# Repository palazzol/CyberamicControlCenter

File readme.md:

# Unofficial Cyberamic Control Center Archive #

This archive contains unofficial information about the Animatronics Control Computer designed the original Chuck E Cheese's Pizza Time Theatre.  The focus of this archive is to document the historical development and capabilities of this machine.

It was reused in several incarnations over it's lifetime:

## Reel to Reel Configuration: ##
* Based on a 6502 processor and a TEAC Tape Deck, this computer controller the shows such as Dolli Dimples, The Beagles, The King, and the Balcony Stage.

## SVHS Configuration #1: ##
* This same hardware was adapted to play media from SVHS Media.

## SVHS Configuration #2: ##
* Upgraded with a M68HC11 processor, and an external media switcher, this continued to be used to play SVHS media.

## DVD Configuration: ##
* Adapted to DVD Media

If you have any more information or experience with this machine, and would like to help document it's history and behavior, please reach out!

# Latest protocol definitions as decoded from ROM images #
https://docs.google.com/spreadsheets/d/1zTHxSJqbsTTEe6A_9ltzb_rc91lcfIUvdmzVYEThIzg/edit?usp=sharing

# Questions: #

We're working on collecting as much information on how the original Pizza Time Theater system worked and have generated some questions:

* Did the original R2R system use 4-track audio at any stores?

Backplane:
* Was the original card cage a different size to accomodate the 0004 rev.a card?
* Why is the lights 50-pin connector recessed on the card compared to the character card?

Are there more board revisions beyond what we have? looking for:
* Audio board 0003 rev.a, rev.b, and beyond rev.c
* Audio board 0033 rev.b and beyond
* Character board 0004 rev.c and beyond
* Character board 0034 rev.b, rev.f and beyond
* Light board 0021 rev.b to rev.e
* Transport board 0020 rev.a
* Did the original transport card take a external uart clock? per the schematic
* Transport board 0020 rev.c
* CPU board 0001 rev.d and beyond 
* Random movements board?
* Board 0002?

Where are any other rom variants beyond what's in this archive?
* (We strongly believe the original balcony stage rom is not represented here)
* How do the other ROMs handle the buttons on the front panel?

Any more un-scanned documentation?
* Are there any more schematics? 
* Any documentation on how to hook up all the shows?

More show tapes on original media?
* More shows decoded?
* What are the formats for the decoding?
* Is there any metadata they missed like potentially more tracks?

Who else to talk to on this subject?

Extra parts we don't have?

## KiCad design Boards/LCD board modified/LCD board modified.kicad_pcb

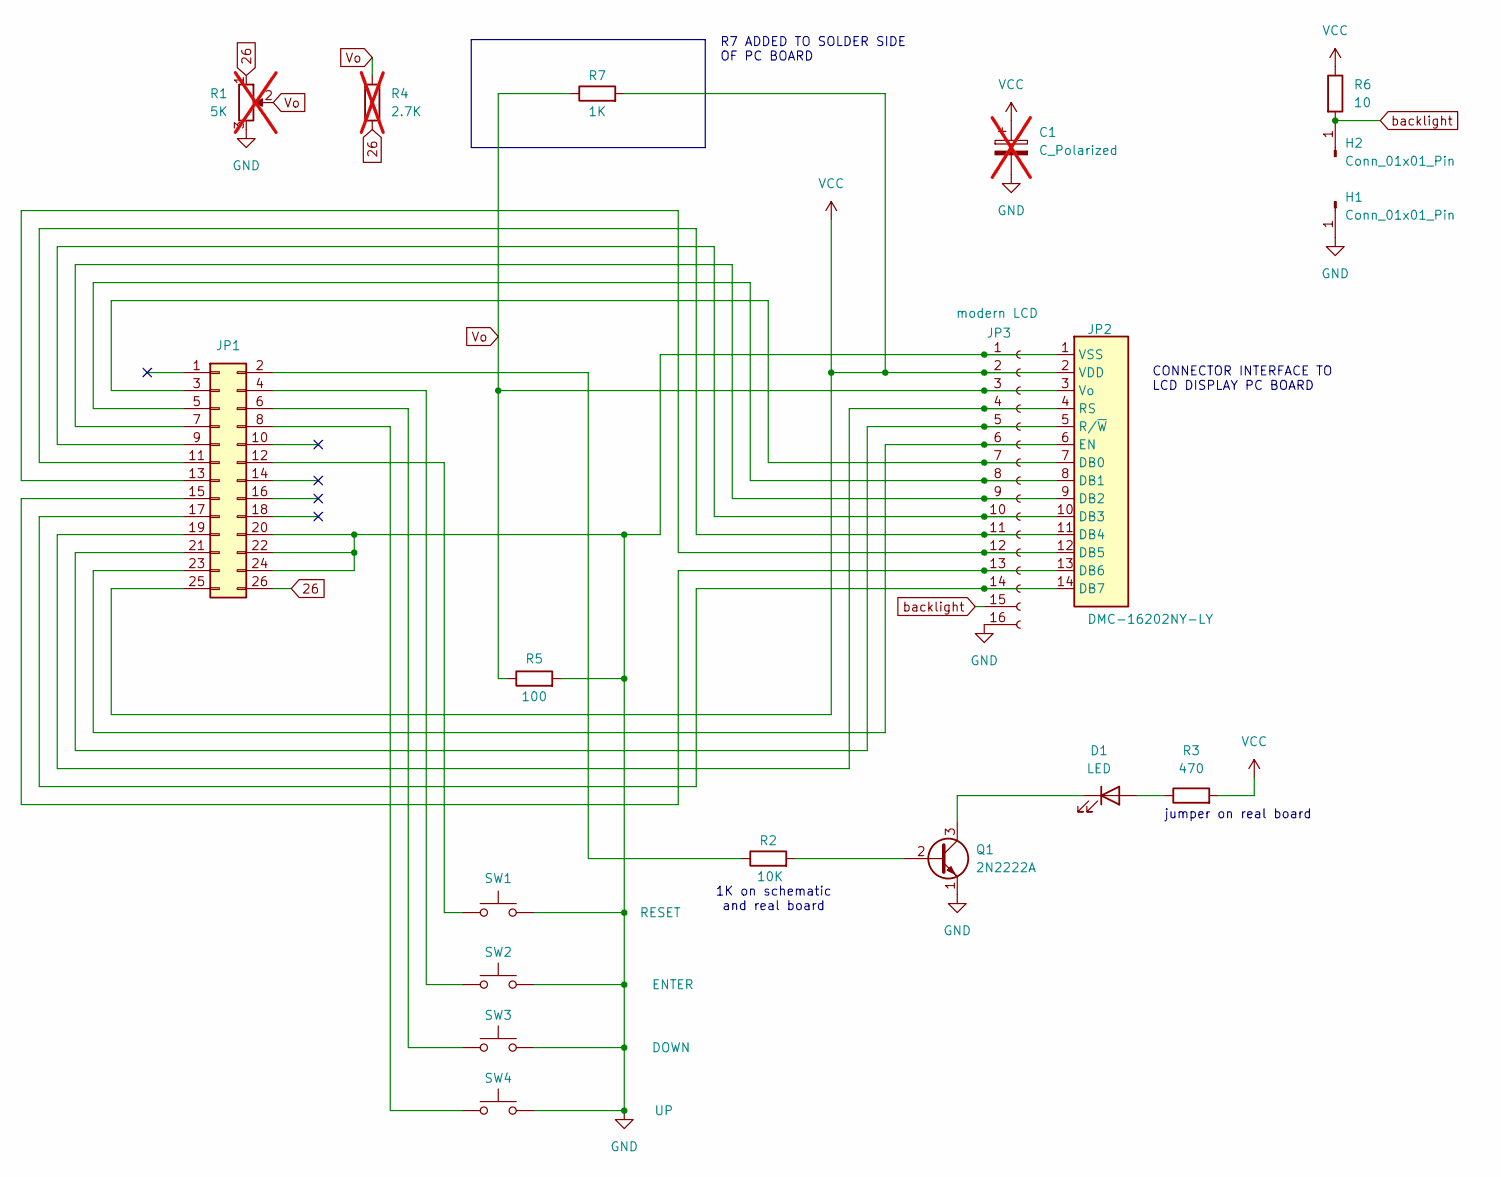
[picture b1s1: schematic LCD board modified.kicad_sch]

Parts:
C1: C_Polarized; CP_Radial_D8.0mm_P5.00mm; not fitted
D1: LED; PinHeader_1x02_P2.54mm_Vertical
H1, H2: Conn_01x01_Pin
JP1: Conn_02x13_Odd_Even; PinHeader_2x13_P2.54mm_Vertical
JP2: DMC-16202NY-LY; CEC LCD
JP3: modern LCD; PinHeader_1x16_P2.54mm_Vertical
Q1: 2N2222A; TO-18-3
R1: 5K; Potentiometer_Bourns_3006P_Horizontal; not fitted
R2: 10K; R_Axial_DIN0207_L6.3mm_D2.5mm_P10.16mm_Horizontal
R3: 470; R_Axial_DIN0207_L6.3mm_D2.5mm_P10.16mm_Horizontal
R4: 2.7K; R_Axial_DIN0207_L6.3mm_D2.5mm_P10.16mm_Horizontal; not fitted
R5: 100; R_Axial_DIN0207_L6.3mm_D2.5mm_P10.16mm_Horizontal
R6: 10; R_Axial_DIN0207_L6.3mm_D2.5mm_P10.16mm_Horizontal
R7: 1K; R_Axial_DIN0207_L6.3mm_D2.5mm_P10.16mm_Horizontal
SW1: RESET; CEC LCD pushbutton
SW2: ENTER; CEC LCD pushbutton
SW3: DOWN; CEC LCD pushbutton
SW4: UP; CEC LCD pushbutton

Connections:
26: JP1.26, R1.1, R4.2
GND: C1.2, H1.1, JP1.20, JP1.22, JP1.24, JP2.1 (VSS), JP3.1, JP3.16, Q1.1 (E), R1.3, R5.2, SW1.1, SW2.2, SW3.2, SW4.2
unnamed: D1.2 (A), R3.1
unnamed: D1.1 (K), Q1.3 (C)
unnamed: JP1.2, R2.1
unnamed: JP1.3, JP2.7 (DB0), JP3.7
unnamed: JP1.4, SW2.1
unnamed: JP1.5, JP2.8 (DB1), JP3.8
unnamed: JP1.6, SW3.1
unnamed: JP1.7, JP2.9 (DB2), JP3.9
unnamed: JP1.8, SW4.1
unnamed: JP1.9, JP2.10 (DB3), JP3.10
unnamed: JP1.11, JP2.11 (DB4), JP3.11
unnamed: JP1.12, SW1.2
unnamed: JP1.13, JP2.12 (DB5), JP3.12
unnamed: JP1.15, JP2.13 (DB6), JP3.13
unnamed: JP1.17, JP2.14 (DB7), JP3.14
unnamed: JP1.19, JP2.4 (RS), JP3.4
unnamed: JP1.21, JP2.5 (R/~W), JP3.5
unnamed: JP1.23, JP2.6 (EN), JP3.6
unnamed: Q1.2 (B), R2.2
VCC: C1.1, JP1.25, JP2.2 (VDD), JP3.2, R3.2, R6.1, R7.2
Vo: JP2.3 (Vo), JP3.3, R1.2, R4.1, R5.1, R7.1
backlight: H2.1, JP3.15, R6.2

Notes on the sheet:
1K on schematic and real board
R7 ADDED TO SOLDER SIDE OF PC BOARD
jumper on real board
CONNECTOR INTERFACE TO LCD DISPLAY PC BOARD

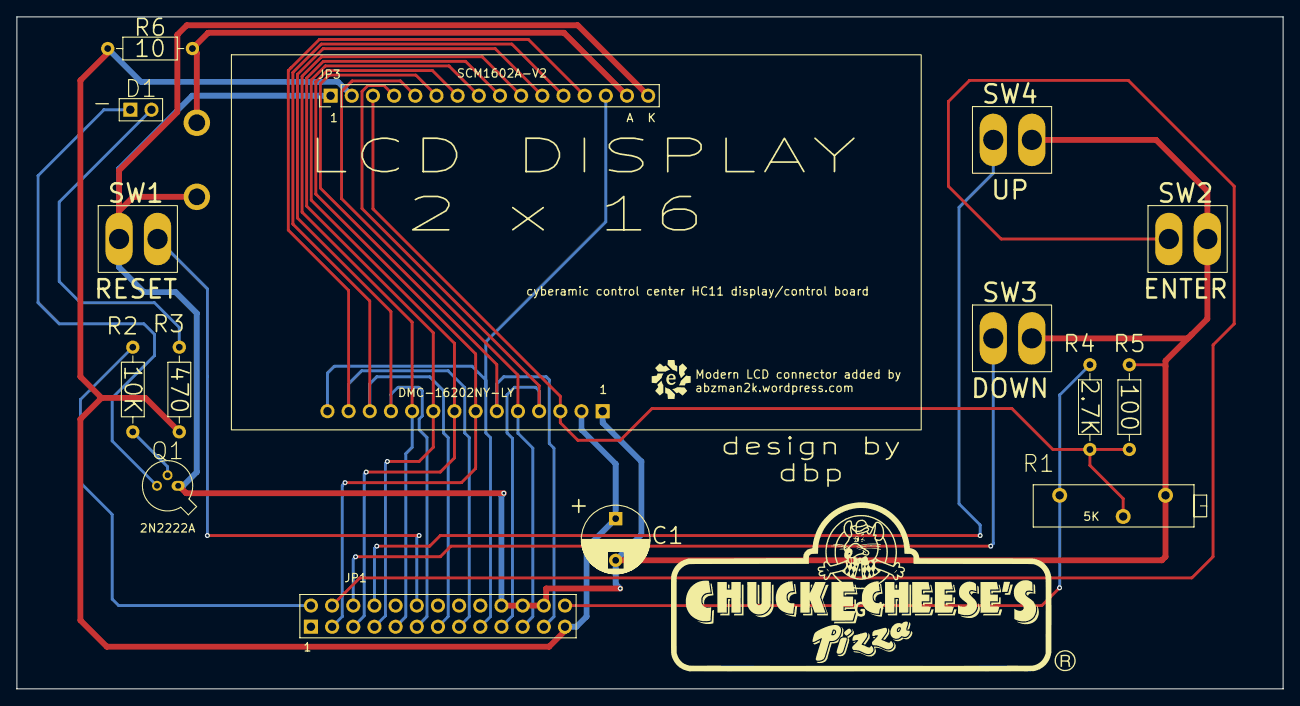
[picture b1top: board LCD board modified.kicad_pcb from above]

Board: 2 copper layers, 151.9 x 80.6 mm, 18 parts (0 on the bottom side), 24 nets.

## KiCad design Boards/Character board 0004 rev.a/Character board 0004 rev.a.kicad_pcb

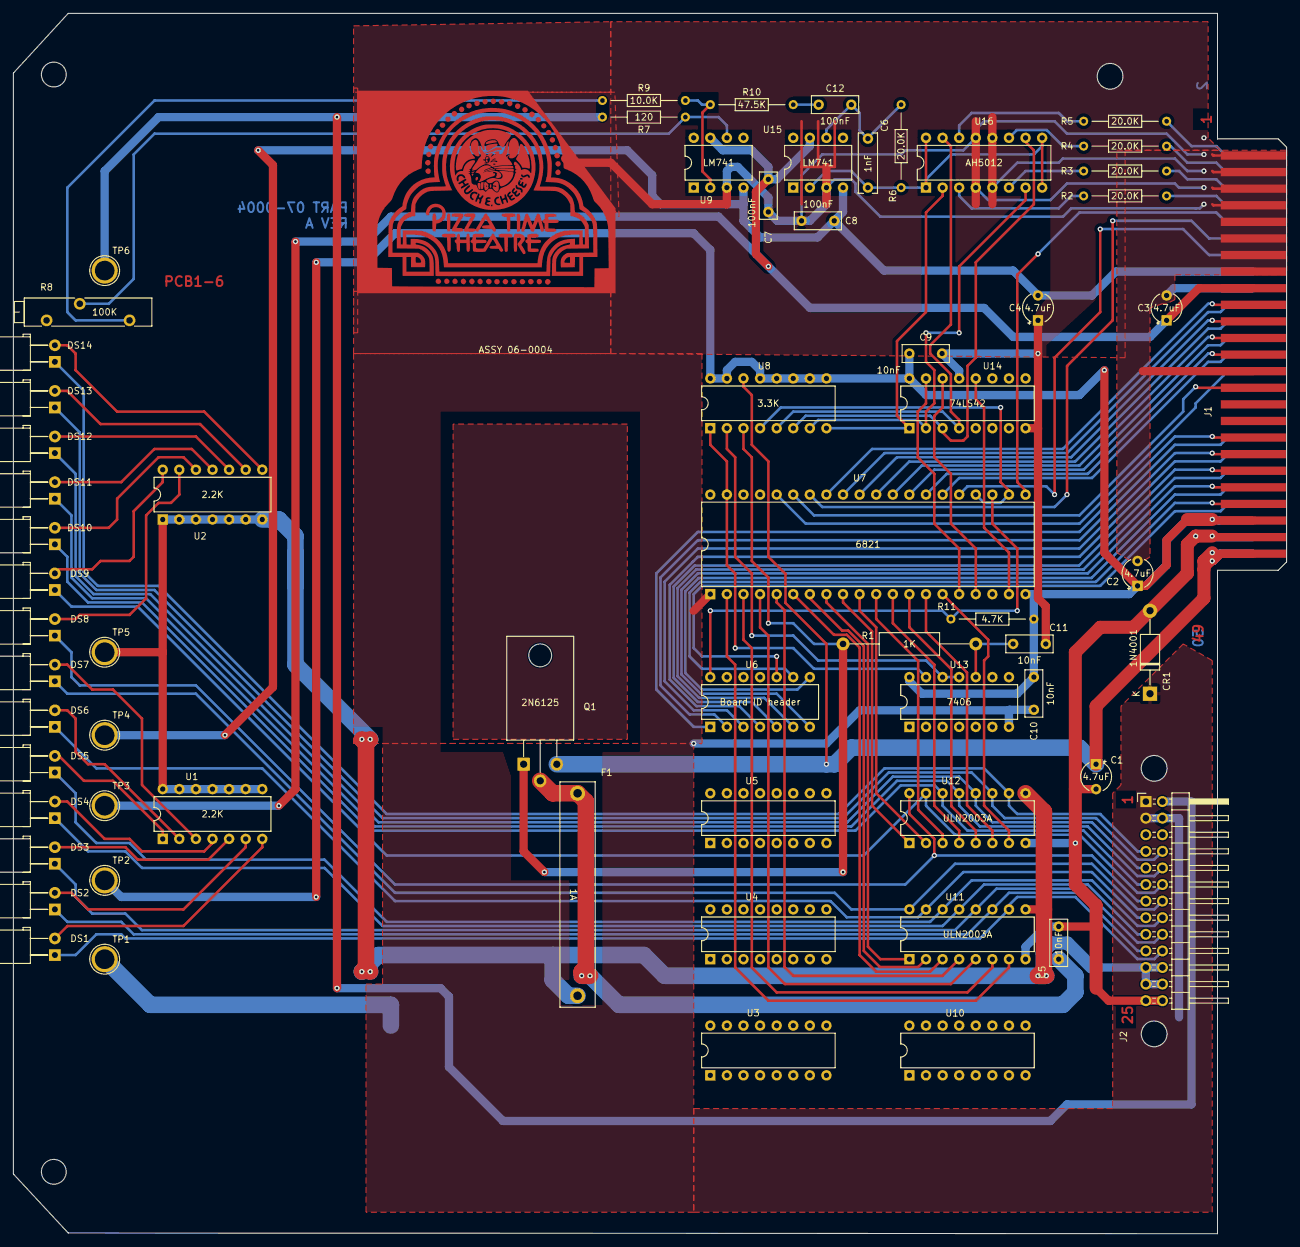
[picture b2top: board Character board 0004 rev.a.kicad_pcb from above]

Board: 2 copper layers, 194.9 x 186.8 mm, 65 parts (0 on the bottom side), 101 nets.

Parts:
C1, C2, C3, C4: 4.7uF; CP_Radial_Tantal_D4mm_P3.81mm
C5, C9, C10, C11: 10nF; C_Rect_L7.0mm_W2.5mm_P5.00mm
C6: 1nF; C_Rect_L9.0mm_W2.7mm_P7.50mm_MKT
C7, C8, C12: 100nF; C_Rect_L7.0mm_W2.5mm_P5.00mm
CR1: 1N4001; D_DO-41_SOD81_P12.70mm_Horizontal
DS1, DS2, DS3, DS4, DS5, DS6, DS7, DS8, DS9, DS10, DS11, DS12, DS13, DS14: LED; LED_D5.0mm_Horizontal_O3.81mm_Z15.0mm reversed
F1: 1A; Fuseholder_Littelfuse_445_030_series_5x30mm
G1: GND; PTT white
J1: card edge; Chuck_E_Cheese_small_card_edge
J2: character connector; PinHeader_2x13_P2.54mm_Horizontal
Q1: 2N6125; TO-220-3_Horizontal_TabDown
R1: 1K; R_Axial_DIN0309_L9.0mm_D3.2mm_P20.32mm_Horizontal
R2, R3, R4, R5, R6: 20.0K; R_Axial_DIN0204_L3.6mm_D1.6mm_P12.7mm_Horizontal
R7: 120; R_Axial_DIN0204_L3.6mm_D1.6mm_P12.7mm_Horizontal
R8: 100K; Potentiometer_Bourns_3005_Horizontal
R9: 10.0K; R_Axial_DIN0204_L3.6mm_D1.6mm_P12.7mm_Horizontal
R10: 47.5K; R_Axial_DIN0204_L3.6mm_D1.6mm_P12.7mm_Horizontal
R11: 4.7K; R_Axial_DIN0204_L3.6mm_D1.6mm_P12.7mm_Horizontal
TP1: GND; TestPoint_Plated_Hole_D3.0mm
TP2: +5; TestPoint_Plated_Hole_D3.0mm
TP3: +12; TestPoint_Plated_Hole_D3.0mm
TP4: -12; TestPoint_Plated_Hole_D3.0mm
TP5: 24; TestPoint_Plated_Hole_D3.0mm
TP6: AUD; TestPoint_Plated_Hole_D3.0mm
U1, U2: 2.2K; DIP-14_W7.62mm
U3, U4, U5, U10: Unused DIP; DIP-16_W7.62mm
U6: Board ID header; DIP-14_W7.62mm
U7: 6821; DIP-40_W15.24mm
U8: 3.3K; DIP-16_W7.62mm
U9, U15: LM741; DIP-8_W7.62mm
U11, U12: ULN2003A; DIP-16_W7.62mm
U13: 7406; DIP-14_W7.62mm
U14: 74LS42; DIP-16_W7.62mm
U16: AH5012; DIP-16_W7.62mm

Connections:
5V: C2.1, C9.1, C10.1, J1.45, J1.46, R11.1, TP2.1, U7.20 (VCC), U8.9 (R8.2), U8.10 (R7.2), U8.11 (R6.2), U8.12 (R5.2), U8.13 (R4.2), U8.15 (R2.2), U8.16 (R1.2), U13.14 (VCC), U14.16 (VCC)
5Vpu: U8.2 (R2.1), U13.11, U13.12
12V: C3.1, C7.1, J1.17, TP3.1, U9.7 (V+), U15.7 (V+)
24R: C1.2, C5.1, CR1.2 (A), J1.47, J1.48, J2.25, J2.26, U11.8 (GND), U12.8 (GND)
24V: C1.1, J1.49, J1.50, Q1.3 (E), U8.14 (R3.2)
24Vout: F1.2, J2.21, J2.22, J2.23, J2.24, TP5.1, U1.8 (R7.2), U1.9 (R6.2), U1.10 (R5.2), U1.11 (R4.2), U1.12 (R3.2), U1.13 (R2.2), U1.14 (R1.2), U2.1 (R1.1), U2.2 (R2.1), U2.3 (R3.1), U2.4 (R4.1), U2.5 (R5.1), U2.6 (R6.1), U2.7 (R7.1), U11.9 (COM), U12.9 (COM)
24Vpu: Q1.1 (B), R1.1, U8.3 (R3.1)
-12V: C4.2, C8.2, J1.16, TP4.1, U9.4 (V-), U15.4 (V-)
A0out: DS1.1 (K), J2.20, U11.10 (O7)
A1out: DS2.1 (K), J2.19, U11.11 (O6)
A2out: DS3.1 (K), J2.18, U11.12 (O5)
A3out: DS4.1 (K), J2.17, U11.13 (O4)
A4out: DS5.1 (K), J2.16, U11.14 (O3)
A5out: DS6.1 (K), J2.15, U11.15 (O2)
A6out: DS7.1 (K), J2.14, U11.16 (O1)
A7out: DS8.1 (K), J2.13, U12.16 (O1)
AUD: J2.2, R7.1, TP6.1
B0out: DS9.1 (K), J2.12, U12.15 (O2)
B1out: DS10.1 (K), J2.11, U12.14 (O3)
B2out: DS11.1 (K), J2.10, U12.13 (O4)
B3out: DS12.1 (K), J2.9, U12.12 (O5)
B4out: DS13.1 (K), J2.8, U12.11 (O6)
B5out: DS14.1 (K), J2.7, U12.10 (O7)
BA0: J1.28, U7.36 (RS0)
BA1: J1.29, U7.35 (RS1)
BGOUT_AGC: J1.8, R2.1
BS1: J1.35, U6.1
BS2: J1.36, U6.2
BS3: J1.37, U6.3
BS4: J1.38, U6.4
BS5: J1.39, U6.5
BS6: J1.40, U6.6
BS7: J1.41, U6.7
BS8: J1.42, U6.8
BS9: J1.43, U6.9
BS10: J1.44, U6.10
CA2: U7.39 (CA2), U8.1 (R1.1), U13.13
CB2: U7.19 (CB2), U14.12 (A3)
CS: U7.22 (CS0), U7.24 (CS1), U8.4 (R4.1)
DBB0: J1.19, U7.33 (D0)
DBB1: J1.20, U7.32 (D1)
DBB2: J1.21, U7.31 (D2)
DBB3: J1.22, U7.30 (D3)
DBB4: J1.23, U7.29 (D4)
DBB5: J1.24, U7.28 (D5)
DBB6: J1.25, U7.27 (D6)
DBB7: J1.26, U7.26 (D7)
GND: C2.2, C3.2, C4.1, C7.2, C8.1, C9.2, C10.2, C11.2, CR1.1 (K), G1.1, J1.1, J1.3, J1.5, J1.7, J1.9, J1.11, J1.13, J1.15, J1.18, J1.27, J2.1, J2.3, J2.4, TP1.1, U7.1 (VSS), U9.3 (+), U13.7 (GND), U14.8 (GND), U14.13 (A2), U15.3 (+), U16.4, U16.5, U16.12, U16.13
unnamed: C11.1, R1.2, U13.10
unnamed: C12.1, R10.2
unnamed: C6.2, C12.2, R6.2, U15.6
unnamed: DS1.2 (A), U1.7 (R7.1)
unnamed: DS2.2 (A), U1.6 (R6.1)
unnamed: DS3.2 (A), U1.5 (R5.1)
unnamed: DS4.2 (A), U1.4 (R4.1)
unnamed: DS5.2 (A), U1.1 (R1.1)
unnamed: DS6.2 (A), U1.2 (R2.1)
unnamed: DS7.2 (A), U1.3 (R3.1)
unnamed: DS8.2 (A), U2.13 (R2.2)
unnamed: DS9.2 (A), U2.14 (R1.2)
unnamed: DS10.2 (A), U2.12 (R3.2)
unnamed: DS11.2 (A), U2.11 (R4.2)
unnamed: DS12.2 (A), U2.10 (R5.2)
unnamed: DS13.2 (A), U2.9 (R6.2)
unnamed: DS14.2 (A), U2.8 (R7.2)
unnamed: C5.2, F1.1, Q1.2 (C)
unnamed: R2.2, U16.3
unnamed: R3.2, U16.6
unnamed: R4.2, U16.11
unnamed: R5.2, U16.14
unnamed: R7.2, R8.2, U9.6
unnamed: R8.1, R9.1
unnamed: R11.2, U6.14, U7.23 (~CS2)
unnamed: R9.2, R10.1, U9.2 (-)
unnamed: U8.8 (R8.1), U14.1 (0), U16.2
unnamed: U8.7 (R7.1), U14.2 (1), U16.7
unnamed: U8.6 (R6.1), U14.3 (2), U16.10
unnamed: U8.5 (R5.1), U14.4 (3), U16.15
unnamed: C6.1, R6.1, U15.2 (-), U16.1, U16.8, U16.9, U16.16
PA0: U7.2 (PA0), U11.7 (I7)
PA1: U7.3 (PA1), U11.6 (I6)
PA2: U7.4 (PA2), U11.5 (I5)
PA3: U7.5 (PA3), U11.4 (I4)
PA4: U7.6 (PA4), U11.3 (I3)
PA5: U7.7 (PA5), U11.2 (I2)
PA6: U7.8 (PA6), U11.1 (I1)
PA7: U7.9 (PA7), U12.1 (I1)
PB0: U7.10 (PB0), U12.2 (I2)
PB1: U7.11 (PB1), U12.3 (I3)
PB2: U7.12 (PB2), U12.4 (I4)
PB3: U7.13 (PB3), U12.5 (I5)
PB4: U7.14 (PB4), U12.6 (I6)
PB5: U7.15 (PB5), U12.7 (I7)
PB6: U7.16 (PB6), U14.15 (A0)
PB7: U7.17 (PB7), U14.14 (A1)
PHI2: J1.14, U7.25 (ENABLE)
R2R_audio_AGC: J1.6, R3.1
R/~W: J1.10, U7.21 (R/~W)
aux1_AGC: J1.2, R5.1
aux2_AGC: J1.4, R4.1
~MRST: J1.12, U7.34 (~RESET)

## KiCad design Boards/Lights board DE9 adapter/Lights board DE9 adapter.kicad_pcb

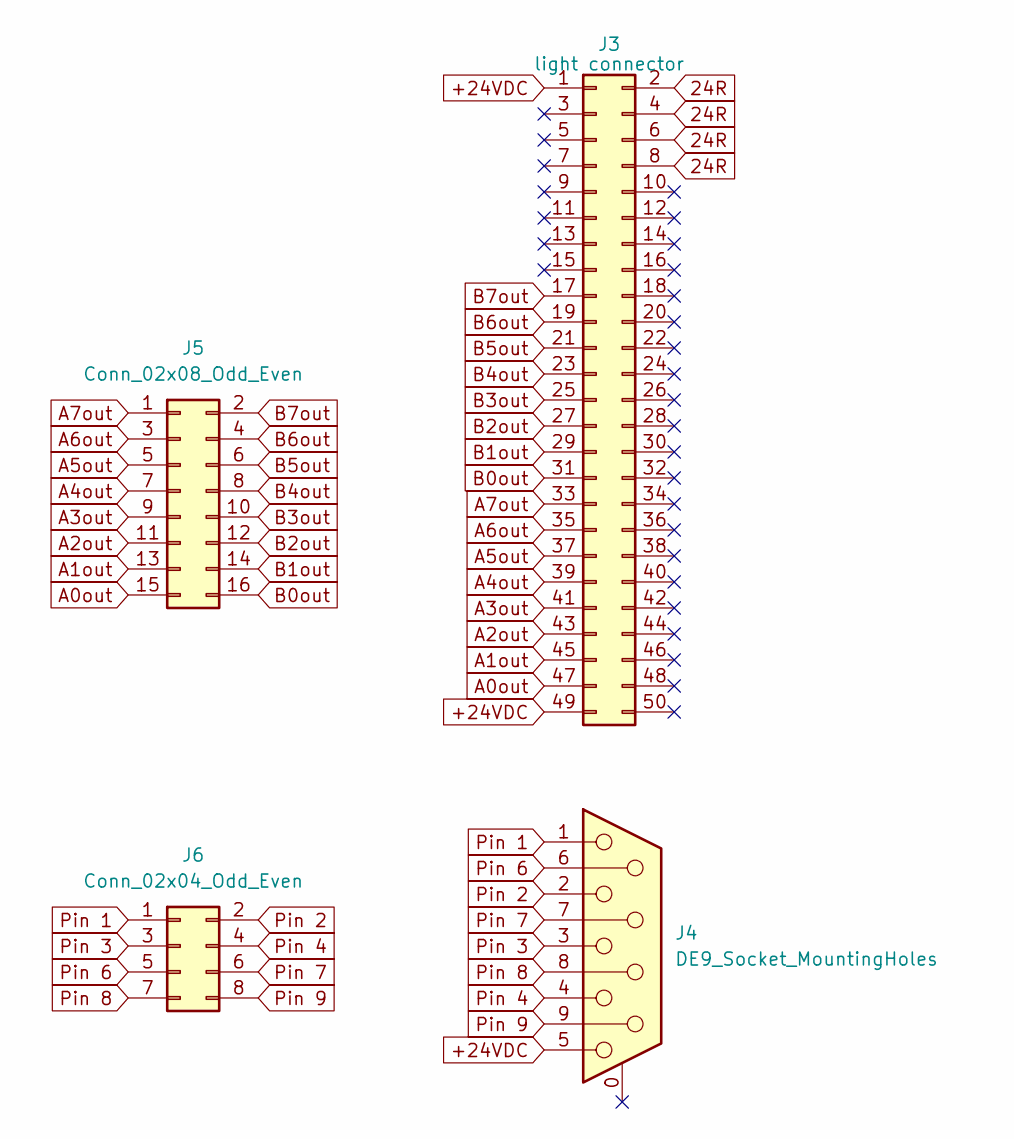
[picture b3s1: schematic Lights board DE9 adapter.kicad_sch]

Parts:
J3: light connector; PinSocket_2x25_P2.54mm_Horizontal
J4: DE9_Socket_MountingHoles; DSUB-9_Socket_Horizontal_P2.77x2.84mm_EdgePinOffset7.70mm_H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
J5: Conn_02x08_Odd_Even; PinHeader_2x08_P2.54mm_Horizontal
J6: Conn_02x04_Odd_Even; PinHeader_2x04_P2.54mm_Horizontal

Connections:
24R: J3.2, J3.4, J3.6, J3.8
+24VDC: J3.1, J3.49, J4.5
A0out: J3.47, J5.15
A1out: J3.45, J5.13
A2out: J3.43, J5.11
A3out: J3.41, J5.9
A4out: J3.39, J5.7
A5out: J3.37, J5.5
A6out: J3.35, J5.3
A7out: J3.33, J5.1
B0out: J3.31, J5.16
B1out: J3.29, J5.14
B2out: J3.27, J5.12
B3out: J3.25, J5.10
B4out: J3.23, J5.8
B5out: J3.21, J5.6
B6out: J3.19, J5.4
B7out: J3.17, J5.2
Pin 1: J4.1, J6.1
Pin 2: J4.2, J6.2
Pin 3: J4.3, J6.3
Pin 4: J4.4, J6.4
Pin 6: J4.6, J6.5
Pin 7: J4.7, J6.6
Pin 8: J4.8, J6.7
Pin 9: J4.9, J6.8

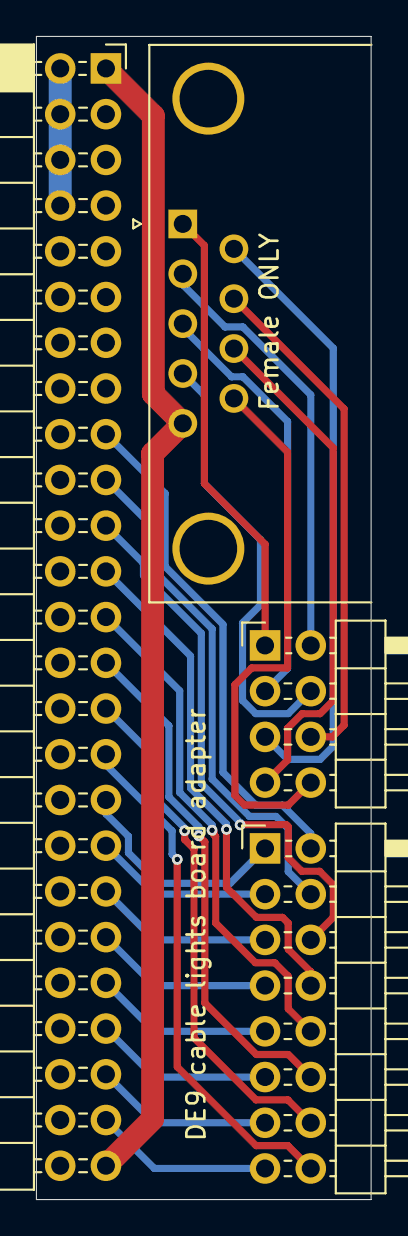
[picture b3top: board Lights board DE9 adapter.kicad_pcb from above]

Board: 2 copper layers, 18.6 x 64.6 mm, 4 parts (0 on the bottom side), 26 nets.

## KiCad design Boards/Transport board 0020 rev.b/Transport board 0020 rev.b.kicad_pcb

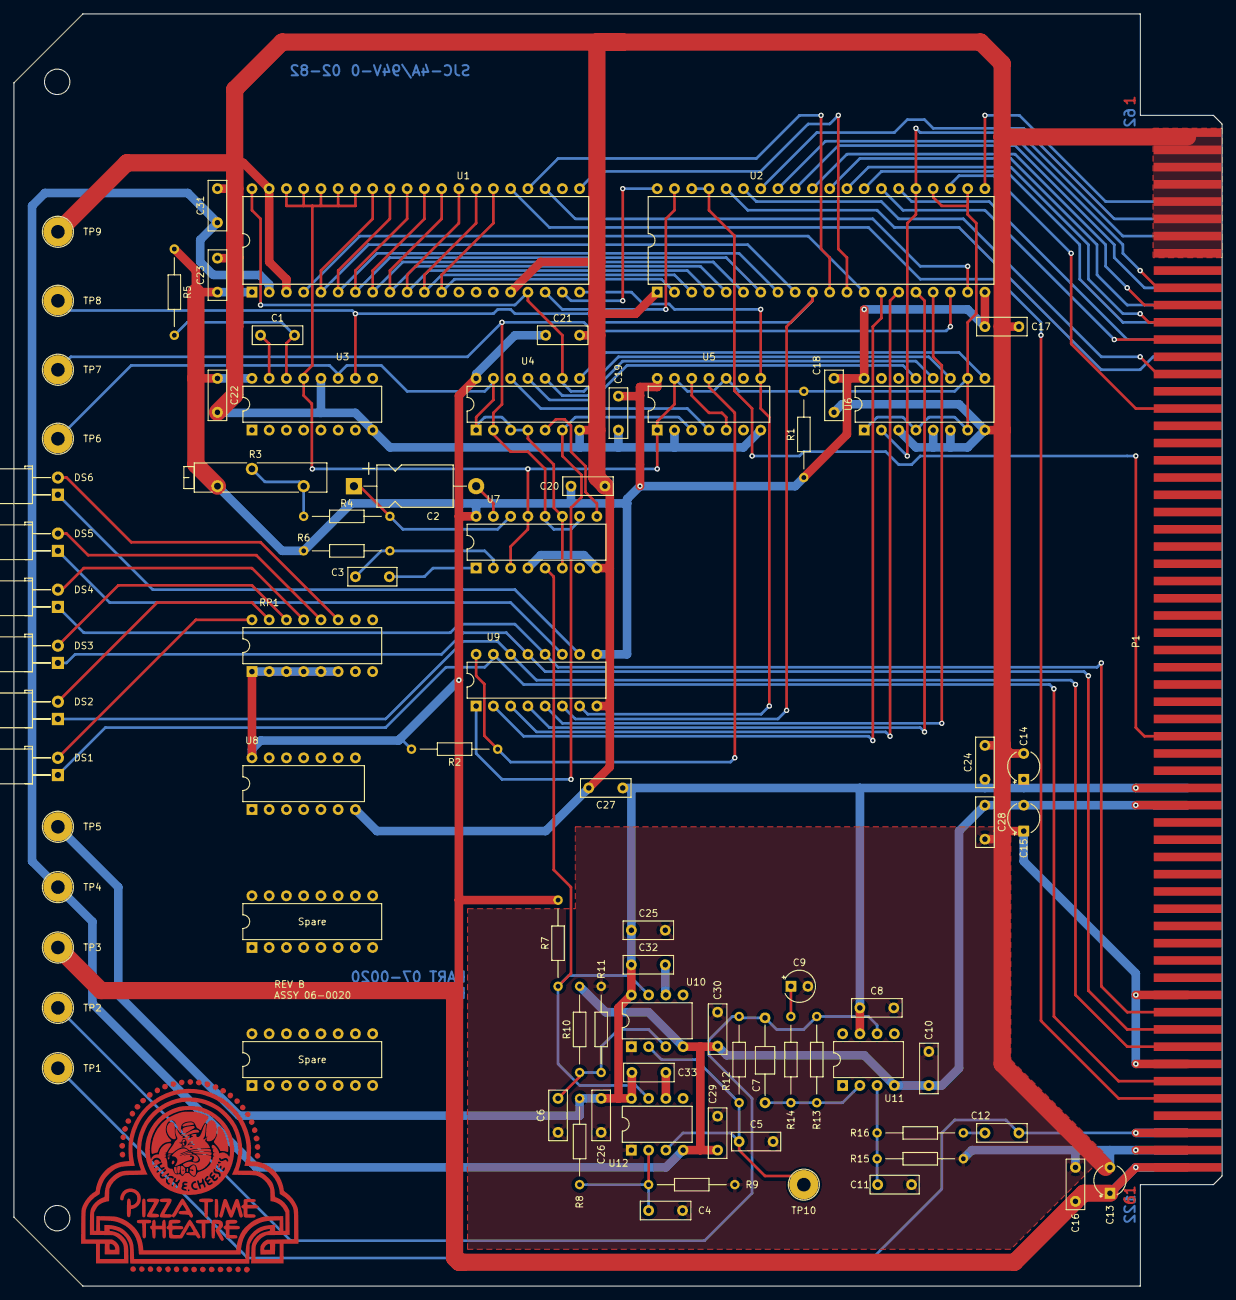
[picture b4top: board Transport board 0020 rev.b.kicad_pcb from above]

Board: 2 copper layers, 177.9 x 187.4 mm, 81 parts (0 on the bottom side), 83 nets.

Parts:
C1: 50nF; C_Rect_L7.2mm_W2.5mm_P5.00mm_FKS2_FKP2_MKS2_MKP2
C2: 39nF; CP_Axial_L11.0mm_D6.0mm_P18.00mm_Horizontal
C3, C5, C11: 100pF; C_Rect_L7.0mm_W2.5mm_P5.00mm
C4, C6, C8, C10, C12, C32, C33: 100nF; C_Rect_L7.2mm_W2.5mm_P5.00mm_FKS2_FKP2_MKS2_MKP2
C7: 3300pF; C_Axial_L3.8mm_D2.6mm_P12.50mm_Horizontal
C9: 4.7uF; CP_Radial_Tantal_D4.5mm_P2.50mm
C13, C14, C15: 4.7uF; CP_Radial_Tantal_D4mm_P3.81mm
C16, C17, C18, C19, C20, C21, C22, C23, C24, C25, C26, C27, C28, C29, C30, C31: 10nF; C_Rect_L7.2mm_W2.5mm_P5.00mm_FKS2_FKP2_MKS2_MKP2
DS1, DS2, DS3, DS4, DS5, DS6: LED; LED_D5.0mm_Horizontal_O3.81mm_Z15.0mm reversed
P1: CEC card edge connector large; Chuck_E_Cheese_large_card_edge
R1, R2, R14: 1K; R_Axial_DIN0204_L3.6mm_D1.6mm_P12.7mm_Horizontal
R3: 5K; Potentiometer_Bourns_3005_Horizontal
R4, R6, R12, R13, R16: 10K; R_Axial_DIN0204_L3.6mm_D1.6mm_P12.7mm_Horizontal
R5: 39K; R_Axial_DIN0204_L3.6mm_D1.6mm_P12.7mm_Horizontal
R7: 470; R_Axial_DIN0204_L3.6mm_D1.6mm_P12.7mm_Horizontal
R8, R10: 470K; R_Axial_DIN0204_L3.6mm_D1.6mm_P12.7mm_Horizontal
R9, R11: 4.7K; R_Axial_DIN0204_L3.6mm_D1.6mm_P12.7mm_Horizontal
R15: 100K; R_Axial_DIN0204_L3.6mm_D1.6mm_P12.7mm_Horizontal
RP1: 330; DIP-16_W7.62mm
TP1: AUDIO IN; TestPoint_Plated_Hole_D3.0mm
TP2: filtered audio; TestPoint_Plated_Hole_D3.0mm
TP3: +5; TestPoint_Plated_Hole_D3.0mm
TP4: -12; TestPoint_Plated_Hole_D3.0mm
TP5: +12; TestPoint_Plated_Hole_D3.0mm
TP6: zero crossings; TestPoint_Plated_Hole_D3.0mm
TP7: bits; TestPoint_Plated_Hole_D3.0mm
TP8: carrier detect; TestPoint_Plated_Hole_D3.0mm
TP9: GND; TestPoint_Plated_Hole_D3.0mm
TP10: second filtered audio; TestPoint_Plated_Hole_D3.0mm
U1: TR1602; DIP-40_W15.24mm
U2: 6821; DIP-40_W15.24mm
U3, U7: DM8602N; DIP-16_W7.62mm
U4: 7410; DIP-14_W7.62mm
U5: 74LS74; DIP-14_W7.62mm
U6: 74161; DIP-16_W7.62mm
U8: Unused DIP; DIP-14_W7.62mm
U9: ULN2003A; DIP-16_W7.62mm
U10, U12: LM311; DIP-8_W7.62mm
U11: LM741; DIP-8_W7.62mm
U14, U15: Spare; DIP-16_W7.62mm

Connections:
+5V: C13.1, C16.1, C17.1, C18.1, C19.1, C20.1, C21.1, C22.1, C23.1, P1.61, P1.122, R1.1, R2.2, R3.3, R5.1, R6.1, R7.1, RP1.1 (R1.1), RP1.2 (R2.1), RP1.3 (R3.1), RP1.4 (R4.1), RP1.5 (R5.1), RP1.6 (R6.1), TP3.1, U1.1 (VSS), U2.20 (VCC), U3.16 (VCC), U4.14 (VCC), U5.14 (VCC), U6.16 (VCC), U7.16 (VCC), U8.14 (R1.2), U9.9 (COM)
+12V: C8.1, C14.1, C24.1, C25.1, C26.1, C27.1, C32.2, C33.2, P1.39, P1.100, R8.2, TP5.1, U10.8 (V+), U11.7 (V+), U12.8 (V+)
-12V: C10.1, C15.2, C28.1, C29.1, C30.1, C31.1, P1.40, P1.101, R10.1, TP4.1, U1.2 (VGG), U10.4 (V-), U11.4 (V-), U12.4 (V-)
A0: P1.75, U2.36 (RS0)
A1: P1.15, U2.35 (RS1)
AUDIO IN: C12.1, P1.59, P1.120, TP1.1
BCLK: U1.17 (RCK), U1.40 (TCK), U4.9, U6.11 (Q3)
CA1: U1.19 (~DR), U2.40 (CA1)
CA2: U1.18 (~DDR), U2.39 (CA2)
CB1: TP7.1, U2.18 (CB1), U4.2, U7.10 (Q), U7.12 (B)
CB2: U1.23 (~THRL), U2.19 (CB2)
D0: P1.10, U2.33 (D0)
D1: P1.71, U2.32 (D1)
D2: P1.11, U2.31 (D2)
D3: P1.72, U2.30 (D3)
D4: P1.12, U2.29 (D4)
D5: P1.73, U2.28 (D5)
D6: P1.13, U2.27 (D6)
D7: P1.74, U2.26 (D7)
DATA OUT: P1.57, U1.25 (TO)
F.F.: DS2.1 (K), P1.54, U9.14 (O3)
GND: C4.2, C5.1, C6.2, C8.2, C9.2, C10.2, C11.1, C13.2, C14.2, C15.1, C16.2, C17.2, C18.2, C19.2, C20.2, C21.2, C22.2, C23.2, C24.2, C25.2, C26.2, C27.2, C28.2, C29.2, C30.2, C31.2, P1.1, P1.2, P1.3, P1.4, P1.5, P1.6, P1.7, P1.8, P1.51, P1.55, P1.60, P1.121, R9.2, R11.2, R15.2, TP9.1, U1.3 (VDD), U1.16 (SFD), U1.39 (SFE), U2.1 (VSS), U3.8 (GND), U3.12 (B), U4.7 (GND), U5.2 (D), U5.7 (GND), U6.3 (D0), U6.5 (D2), U6.6 (D3), U6.8 (GND), U7.4 (B), U7.8 (GND), U8.7 (R7.1), U9.8 (GND), U10.1 (GND), U12.1 (GND)
unnamed: C7.2, R12.1, R13.1, TP2.1, U11.6
unnamed: C9.1, R14.2
unnamed: C12.2, R16.1
unnamed: DS1.2 (A), RP1.16 (R1.2)
unnamed: DS2.2 (A), RP1.15 (R2.2)
unnamed: DS3.2 (A), RP1.14 (R3.2)
unnamed: DS4.2 (A), RP1.13 (R4.2)
unnamed: DS5.2 (A), RP1.12 (R5.2)
unnamed: DS5.1 (K), U9.11 (O6)
unnamed: DS6.2 (A), RP1.11 (R6.2)
unnamed: DS6.1 (K), U9.10 (O7)
unnamed: R3.1, R3.2, R4.1
unnamed: U1.20 (RI), U5.8 (~Q), U9.7 (I7)
unnamed: TP6.1, U3.11 (A), U4.1, U4.3, U4.4, U4.13, U7.6 (Q), U7.11 (A)
unnamed: C1.2, U3.15 (Cext)
unnamed: C1.1, R5.2, U3.14 (RCext)
unnamed: U5.5 (Q), U5.12 (D)
unnamed: U4.12, U5.4 (~S)
unnamed: U4.11, U6.13 (Q1)
unnamed: U4.10, U6.12 (Q2)
unnamed: U4.8, U6.9 (~PE)
unnamed: C2.2, U7.15 (Cext)
unnamed: C2.1, R4.2, U7.14 (RCext)
unnamed: U4.5, U7.9 (~Q)
unnamed: R7.2, U7.5 (A), U10.7, U12.7
unnamed: C3.1, U7.1 (Cext)
unnamed: C3.2, R6.2, U7.2 (RCext)
unnamed: C5.2, R12.2, TP10.1, U10.2 (+), U12.3 (-)
unnamed: C6.1, R10.2, R11.1, U10.3 (-)
unnamed: C32.1, U10.6 (STRB)
unnamed: C11.2, R15.1, R16.2, U11.3 (+)
unnamed: C7.1, R13.2, R14.1, U11.2 (-)
unnamed: C4.1, R8.1, R9.1, U12.2 (+)
unnamed: C33.1, U12.6 (STRB)
PA0: U1.12 (R0), U1.26 (T0), U2.2 (PA0)
PA1: U1.11 (R1), U1.27 (T1), U2.3 (PA1)
PA2: U1.10 (R2), U1.28 (T2), U2.4 (PA2)
PA3: U1.9 (R3), U1.29 (T3), U2.5 (PA3)
PA4: U1.8 (R4), U1.30 (T4), U2.6 (PA4)
PA5: U1.7 (R5), U1.31 (T5), U2.7 (PA5)
PA6: U1.6 (R6), U1.32 (T6), U2.8 (PA6)
PA7: U1.5 (R7), U1.33 (T7), U2.9 (PA7)
PB0: TP8.1, U2.10 (PB0), U3.10 (Q), U9.6 (I6)
PB1: U1.24 (TRE), U2.11 (PB1)
PB2: U1.21 (MR), U2.12 (PB2)
PB3: U1.4 (~RCVEN), U2.13 (PB3)
PB4: U2.14 (PB4), U9.2 (I2)
PB5: U2.15 (PB5), U9.3 (I3)
PB6: U2.16 (PB6), U9.4 (I4)
PB7: U2.17 (PB7), U9.5 (I5)
PHI2: P1.68, U2.25 (ENABLE), U6.2 (CP)
PLAY: DS4.1 (K), P1.52, U9.12 (O5)
R.W.: DS3.1 (K), P1.53, U9.13 (O4)
R/~W: P1.66, U2.21 (R/~W)
STOP: DS1.1 (K), P1.56, U9.15 (O2)
U9in: U4.6, U5.3 (C), U9.1 (I1)
U9out: R2.1, U5.11 (C), U9.16 (O1)
pup: R1.2, U1.34 (CRL), U1.35 (PI), U1.36 (SBS), U1.37 (WS1), U1.38 (WS2), U2.22 (CS0), U2.24 (CS1), U3.13 (Clr), U5.1 (~R), U5.10 (~S), U5.13 (~R), U6.1 (~MR), U6.4 (D1), U6.7 (CEP), U6.10 (CET), U7.3 (Clr), U7.13 (Clr)
/IRLQ: P1.36, U2.37 (~IRQB), U2.38 (~IRQA)
/RESET: P1.67, U2.34 (~RESET)
/SEL0: P1.17, U2.23 (~CS2)
